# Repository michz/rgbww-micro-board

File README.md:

RGBWW-micro-board
=================

Miniature version of [patrickjahns](https://github.com/patrickjahns/)'
[esp-rgbww-controller](https://github.com/patrickjahns/esp_rgbww_controller).

(No power output stage on board!)

LICENSE
-------

This is open hardware. Use it wisely in a fair way.

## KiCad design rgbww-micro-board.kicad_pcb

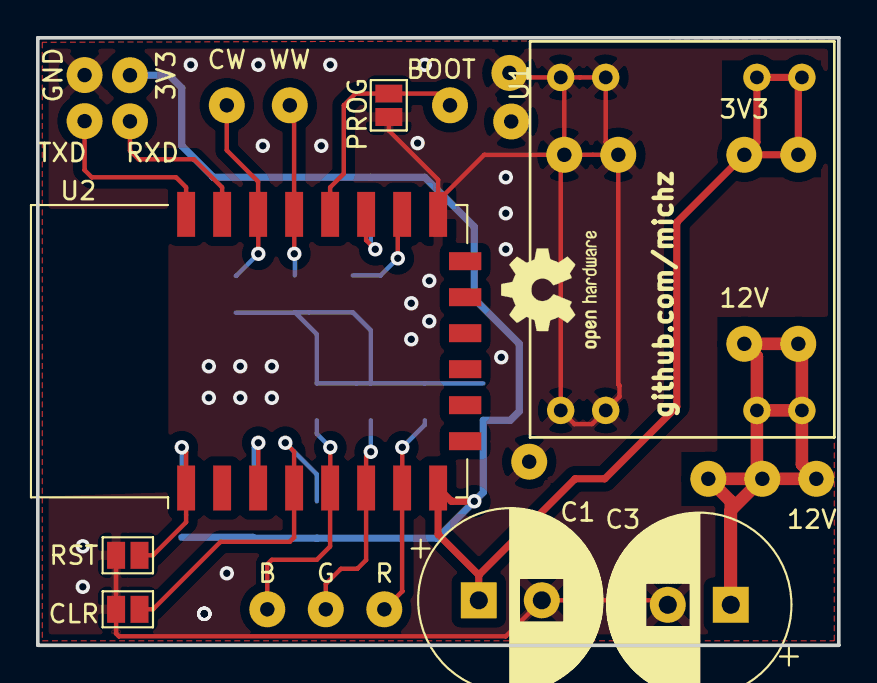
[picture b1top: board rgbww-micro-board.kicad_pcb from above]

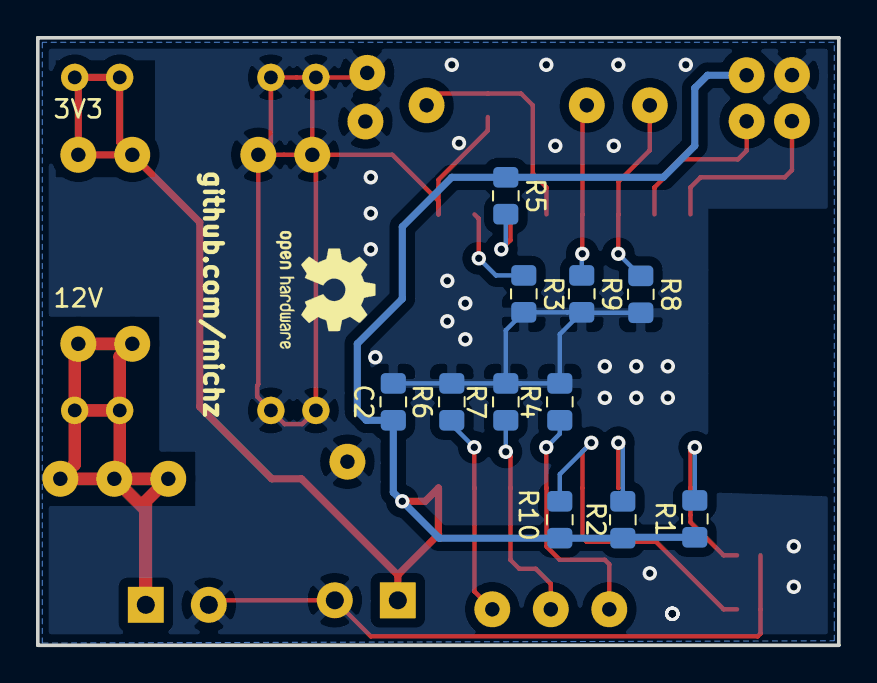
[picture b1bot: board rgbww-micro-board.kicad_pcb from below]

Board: 2 copper layers, 44.5 x 33.8 mm, 33 parts (11 on the bottom side), 16 nets.

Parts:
3V3, 3V3#2, 3V3#3: 3.3V; SolderWirePad_1x01_Drill0.8mm
12V, 12V#2, 12V#3: +12V; SolderWirePad_1x01_Drill0.8mm
B: B; SolderWirePad_1x01_Drill0.8mm
BOOT: BOOT; SolderWirePad_1x01_Drill0.8mm
C1: 1000u; CP_Radial_D10.0mm_P3.50mm
C2: 100n; C_0805_2012Metric_Pad1.15x1.40mm_HandSolder
C3: 100u; CP_Radial_D10.0mm_P3.50mm
CLR: CLR; SolderJumper-2_P1.3mm_Open_Pad1.0x1.5mm
CW: CW; SolderWirePad_1x01_Drill0.8mm
G: G; SolderWirePad_1x01_Drill0.8mm
GND: GND; SolderWirePad_1x01_Drill0.8mm
PROG: PROG; SolderJumper-2_P1.3mm_Open_Pad1.0x1.5mm
R: R; SolderWirePad_1x01_Drill0.8mm
R1, R2, R3, R4, R5, R6, R7, R8, R9, R10: 10k; R_0805_2012Metric_Pad1.15x1.40mm_HandSolder
RST: RST; SolderJumper-2_P1.3mm_Open_Pad1.0x1.5mm
RXD: RXD; SolderWirePad_1x01_Drill0.8mm
TXD: TXD; SolderWirePad_1x01_Drill0.8mm
U1: dcdc-module; DCDC
U2: ESP-12E
WW: WW; SolderWirePad_1x01_Drill0.8mm

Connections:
+3V3: 3V3.1, 3V3#2.1, 3V3#3.1, C1.1, C2.1, R1.1, R2.1, R5.1, R10.1, U1.5, U1.6, U2.8
+12V: 12V.1, 12V#2.1, 12V#3.1, C3.1, U1.1, U1.2
/B: B.1, R4.1, U2.5
/BOOT: BOOT.1, PROG.1, U2.18
/CW: CW.1, R8.1, U2.20
/G: G.1, R7.1, U2.6
/R: R.1, R6.1, U2.7
/RXD: RXD.1, U2.21
/TXD: TXD.1, U2.22
/WW: R9.1, U2.19, WW.1
GND: C1.2, C2.2, C3.2, CLR.2, GND.1, PROG.2, R3.2, R4.2, R6.2, R7.2, R8.2, R9.2, RST.2, U1.3, U1.4, U1.7, U1.8, U2.15
unnamed: R1.2, RST.1, U2.1
unnamed: CLR.1, R10.2, U2.4
unnamed: R2.2, U2.3
unnamed: R3.1, U2.16
unnamed: R5.2, U2.17

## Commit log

2019-05-18 add more gnd pads
2019-05-18 add README with credits
2019-05-18 add a note about missing power output stage
